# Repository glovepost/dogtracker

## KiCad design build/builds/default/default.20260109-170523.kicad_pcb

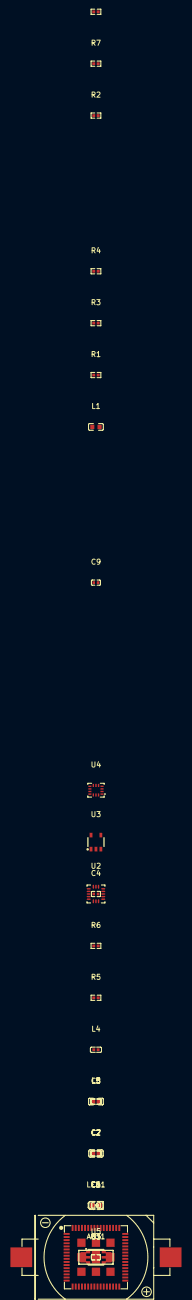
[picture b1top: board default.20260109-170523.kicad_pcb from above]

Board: 2 copper layers, 30 parts (0 on the bottom side), 15 nets, no tracks yet.

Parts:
ANT1: ANT-SMD_3P-L6.0-W2.0_M620720
B1: BAT-TH_CR2032-BS-6-1
C1, C2: 100nF ±10% 50V X7R; C0603
C3, C9: 4.7µF ±10% 10V X5R; C0402
C4, C5, C6, C7, C8: 100nF ±10% 50V X7R; C0402
L1, L5: 10µH ±20% 30MHz 50mA 1.17Ω; L0603
L2, L3, L4: L0402
LED1: LED0603-RD
R1, R2, R4, R5: 10kΩ ±1% 62.5mW; R0402
R3: R0402
R6: 1kΩ ±5% 62.5mW; R0402
R7, R8: 4.7kΩ ±5% 62.5mW; R0402
U1: LGA-73_L12.0-W12.0-P0.60-TL
U2: LGA-16_L3.0-W3.0-P0.50-TL
U3: SOT-23-5_L2.9-W1.5-P0.95-LS2.8-BL
U4: LGA-14_L3.0-W2.5-P0.50-BR
U5: WSON-6_L3.0-W3.0-P1.00-TL-EP

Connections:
A: LED1.2, R6.2
DRDY_INT: U1.19, U5.4
Feed: ANT1.1, C2.1, L5.2
INT1: U1.15, U2.11
RF_OUT: C1.1, L5.1, U1.37
activation: R5.2, U1.42
adc_ntc: R3.1, R4.2, U1.45
footprint-INT2-0: U1.58, U4.9
footprint-INT2-1: U1.14, U2.9
gnd: ANT1.3, B1.2, C1.2, C2.2, C3.2, C4.2, C5.2, C6.2, C7.2, C8.2, C9.2, LED1.1, R1.2, R3.2, U1.12, U1.28, U1.35, U1.36, U1.38, U1.39, U1.46, U1.47, U1.52, U1.56, U1.65, U1.66, U1.67, U1.68, U1.69, U1.70, U1.71, U1.72, U1.73, U2.5, U2.12, U3.2, U3.5, U4.4, U4.6, U4.7, U5.2
i2c_scl: R8.2, U1.8, U2.4, U3.1, U4.13, U5.6
i2c_sda: R7.2, U1.17, U2.6, U3.3, U4.14, U5.1
led_status: R6.1, U1.16
vbat: B1.1, L2.1, U1.4
vcc: C3.1, C4.1, C5.1, C6.1, C7.1, C8.1, C9.1, L1.1, L1.2, L2.2, L3.1, L3.2, L4.1, L4.2, R1.1, R4.1, R5.1, R7.1, R8.1, U1.3, U1.7, U1.53, U1.54, U1.55, U2.1, U2.14, U3.4, U4.5, U4.8, U5.5

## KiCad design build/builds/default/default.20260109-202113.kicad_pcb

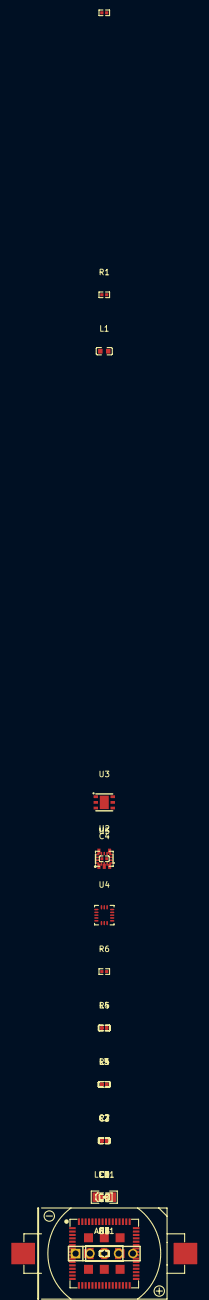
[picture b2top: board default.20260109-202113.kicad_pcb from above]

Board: 2 copper layers, 29 parts (0 on the bottom side), 20 nets, no tracks yet.

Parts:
ANT1: ANT-SMD_3P-L6.0-W2.0_M620720
B1: BAT-TH_CR2032-BS-6-1
C1, C2: 5.6pF 50V C0G; C0402
C3, C6: 4.7µF ±10% 10V X5R; C0402
C4, C5, C7, C8: 100nF ±10% 50V X7R; C0402
C9: R1206
H1: HDR-TH_5P-P2.54-V-M
L1: 10µH ±20% 30MHz 50mA 1.17Ω; L0603
L2, L3, L4: L0402
L5: 4.3nH 6GHz 750mA 140mΩ; L0402
LED1: LED0603-RD
R1, R3: 10kΩ ±1% 62.5mW; R0402
R2: R0402
R4: 1kΩ ±5% 62.5mW; R0402
R5, R6: 4.7kΩ ±5% 62.5mW; R0402
U1: LGA-73_L12.0-W12.0-P0.60-TL
U2: SOT-23-5_L2.9-W1.5-P0.95-LS2.8-BL
U3: WSON-6_L3.0-W3.0-P1.00-TL-EP
U4: LGA-16_L3.0-W3.0-P0.50-TL
U5: LGA-14_L3.0-W2.5-P0.50-BR

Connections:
A: LED1.2, R4.2
DRDY_INT: U1.19, U3.4
Feed: ANT1.1, C2.1, L5.2
INT1: U1.15, U4.11
RF_OUT: C1.1, L5.1, U1.37
activation: R3.2, U1.42
adc_ntc: R1.2, R2.1, U1.45
c1-vcc: C3.1, C4.1, H1.1, L2.2, L3.1, L4.1, R1.1, R3.1, R5.1, R6.1
c5-vcc: C7.1, C8.1, L4.2, U2.4, U3.5, U4.1, U4.14, U5.5, U5.8
footprint-INT2-0: U1.58, U5.9
footprint-INT2-1: U1.14, U4.9
gnd: ANT1.3, B1.2, C1.2, C2.2, C3.2, C4.2, C5.2, C6.2, C7.2, C8.2, C9.2, H1.5, LED1.1, R2.2, U1.12, U1.28, U1.35, U1.36, U1.38, U1.39, U1.46, U1.47, U1.52, U1.56, U1.65, U1.66, U1.67, U1.68, U1.69, U1.70, U1.71, U1.72, U1.73, U2.2, U2.5, U3.2, U4.5, U4.12, U5.4, U5.6, U5.7
i2c_scl: R6.2, U1.8, U2.1, U3.6, U4.4, U5.13
i2c_sda: R5.2, U1.17, U2.3, U3.1, U4.6, U5.14
led_status: R4.1, U1.16
nrst: H1.4, U1.44
swclk: H1.3, U1.2
swdio: H1.2, U1.1
vbat: B1.1, C9.1, L2.1, U1.4
vcc_mcu: C5.1, C6.1, L3.2, U1.3, U1.7, U1.53, U1.54, U1.55

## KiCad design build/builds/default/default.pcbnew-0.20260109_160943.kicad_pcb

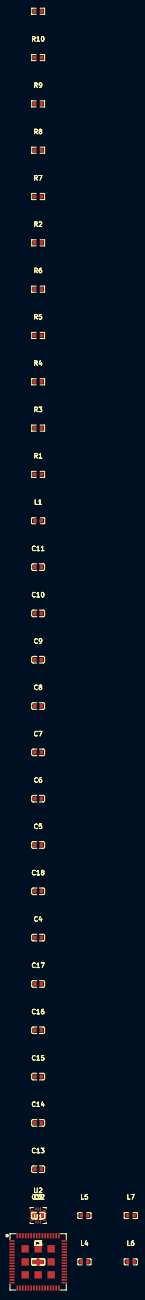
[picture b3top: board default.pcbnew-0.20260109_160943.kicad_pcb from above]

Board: 2 copper layers, 38 parts (0 on the bottom side), 4 nets, no tracks yet.

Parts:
C1, C2: L0603
C3, C4, C5, C6, C7, C8, C9, C10, C11, C12, C13, C14, C15, C16, C17, C18: 100nF ±10% 50V X7R; C0603
L1, L2, L3, L4, L5, L6, L7: 10µH ±20% 30MHz 50mA 1.17Ω; L0603
R1, R2, R3, R4, R5, R6, R7, R8, R9, R10, R11: 10kΩ ±1% 100mW; R0603
U1: LGA-73_L12.0-W12.0-P0.60-TL
U2: LGA-16_L3.0-W3.0-P0.50-TL

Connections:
gnd: C1.2, C2.2, C3.2, C4.2, C5.2, C6.2, C7.2, C8.2, C9.2, C10.2, C11.2, C12.2, C13.2, C14.2, C15.2, C16.2, C17.2, C18.2, U1.12, U1.28, U1.35, U1.36, U1.38, U1.39, U1.46, U1.47, U1.52, U1.56, U1.65, U1.66, U1.67, U1.68, U1.69, U1.70, U1.71, U1.72, U1.73, U2.5, U2.12
i2c_scl: R8.2, U1.8, U2.4
i2c_sda: R7.2, U1.17, U2.6
vcc: C1.1, C2.1, C3.1, C4.1, C5.1, C6.1, C7.1, C8.1, C9.1, C10.1, C11.1, C12.1, C13.1, C14.1, C15.1, C16.1, C17.1, C18.1, R7.1, R8.1, U1.3, U1.7, U1.53, U1.54, U1.55, U2.1, U2.14
